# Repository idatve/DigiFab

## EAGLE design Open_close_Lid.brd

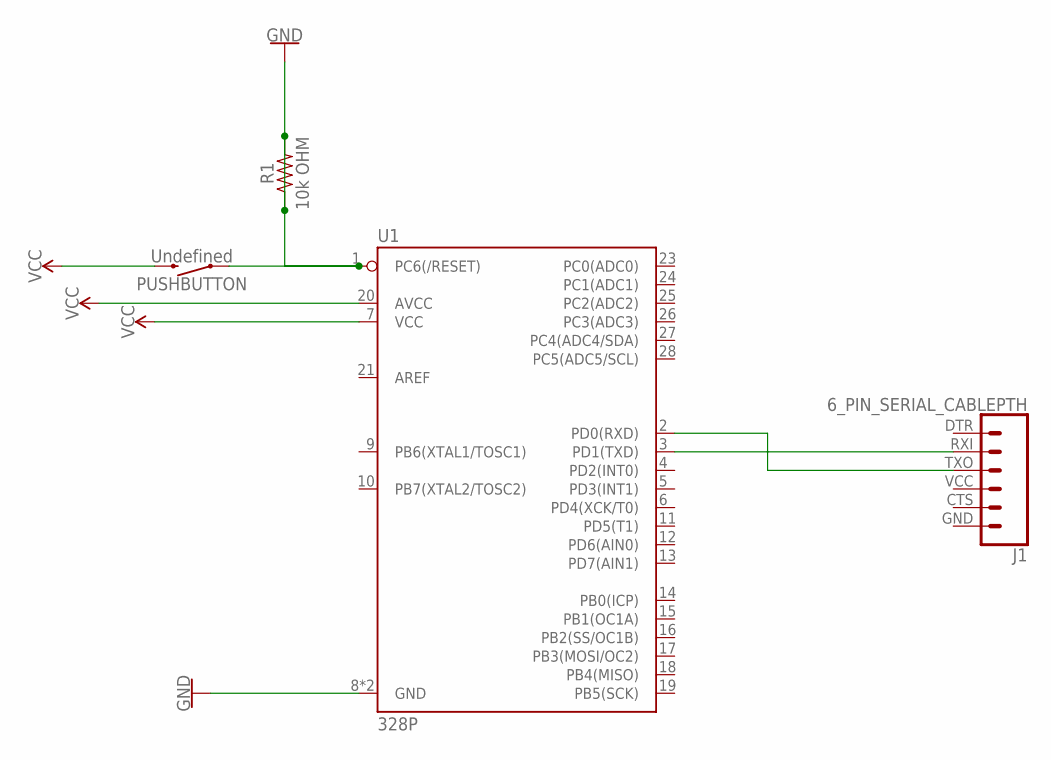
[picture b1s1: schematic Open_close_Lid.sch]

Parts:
J1: 6_PIN_SERIAL_CABLEPTH; FTDI_BASIC
PUSHBUTTON: Undefined; TACTILE_SWITCH_PTH_6.0MM
R1: 10k OHM; AXIAL-0.3
U1: 328P; DIP28

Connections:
GND: PUSHBUTTON.1, R1.P$1 (1), R1.P$2 (2), U1.1 (PC6(/RESET)), U1.8 (GND), U1.22 (GND)
unnamed: J1.TXO (3), U1.2 (PD0(RXD))
unnamed: J1.RXI (2), U1.3 (PD1(TXD))
VCC: PUSHBUTTON.3 (2), U1.7 (VCC), U1.20 (AVCC)

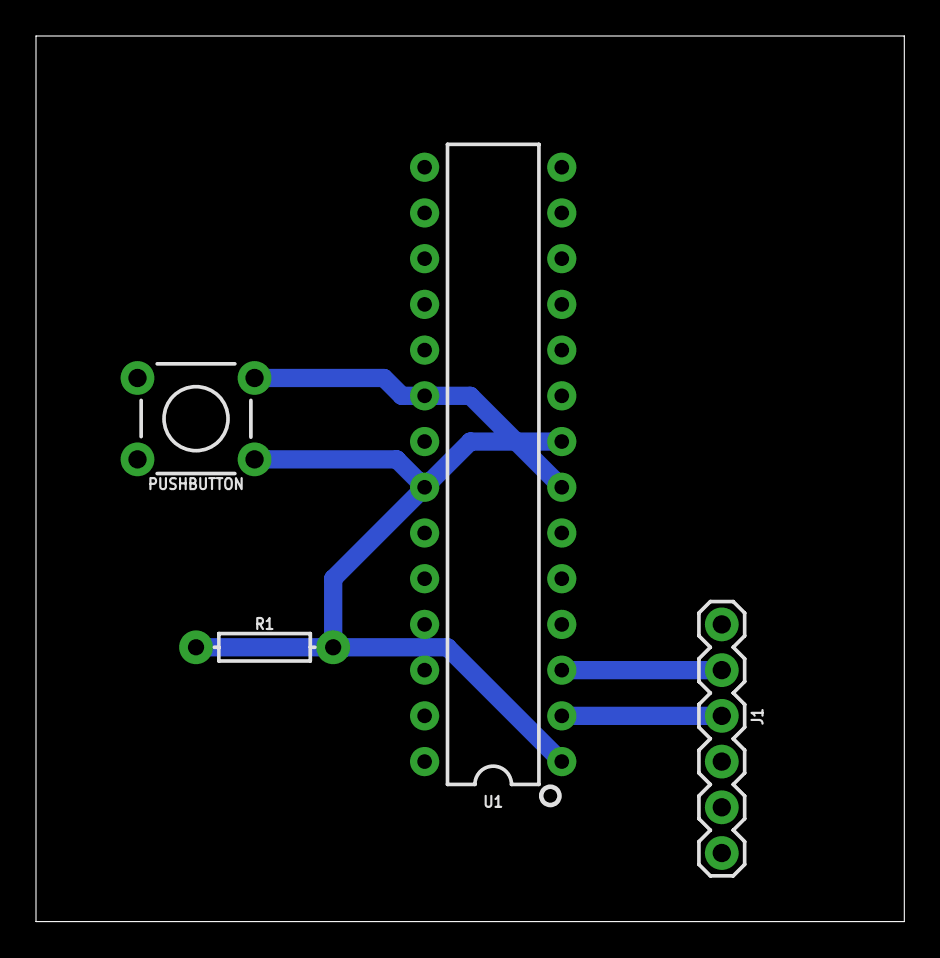
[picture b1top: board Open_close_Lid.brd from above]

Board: 2 copper layers, 48.2 x 49.2 mm, 4 parts (0 on the bottom side), 4 nets.

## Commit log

2022-09-29 changed name on file
2022-09-29 home to index name change
2022-11-10 Published assignment 2
2023-02-01 updated project 2
2023-02-19 Add files via upload
    Arduino Uno code - blinking LED lights
2023-02-19 Project3
2023-03-25 Create PCB Design
2023-03-26 Oblig 4
2023-05-29 Eksamensprosjekt
2023-05-29 Eksamensmappe
2023-05-29 Small changes

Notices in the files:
parts and their libraries:
SparkFun-Connectors: Licensing: Creative Commons ShareAlike 4.0 International - https://creativecommons.org/licenses/by-sa/4.0
